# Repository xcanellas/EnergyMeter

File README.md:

## Descripción

Desarrollo completo, desde la tarjeta electrónica hasta el firmware, de un dispositivo que nos permite leer el consumo eléctrico y enviarlo mediante MQTT al servidor.

## Autor
**Xavier Cañellas**

* [Linkedin] (https://www.linkedin.com/in/xcanellas/)
* [Proyectos personales] (http://xnmundo.com/)

## Contacto
Si quieres contactarme puedes escribirme a xcanellas@xnmundo.com para consultas.

## Lincencia
MIT Public License v3.0
No puede usarse comercialmente.

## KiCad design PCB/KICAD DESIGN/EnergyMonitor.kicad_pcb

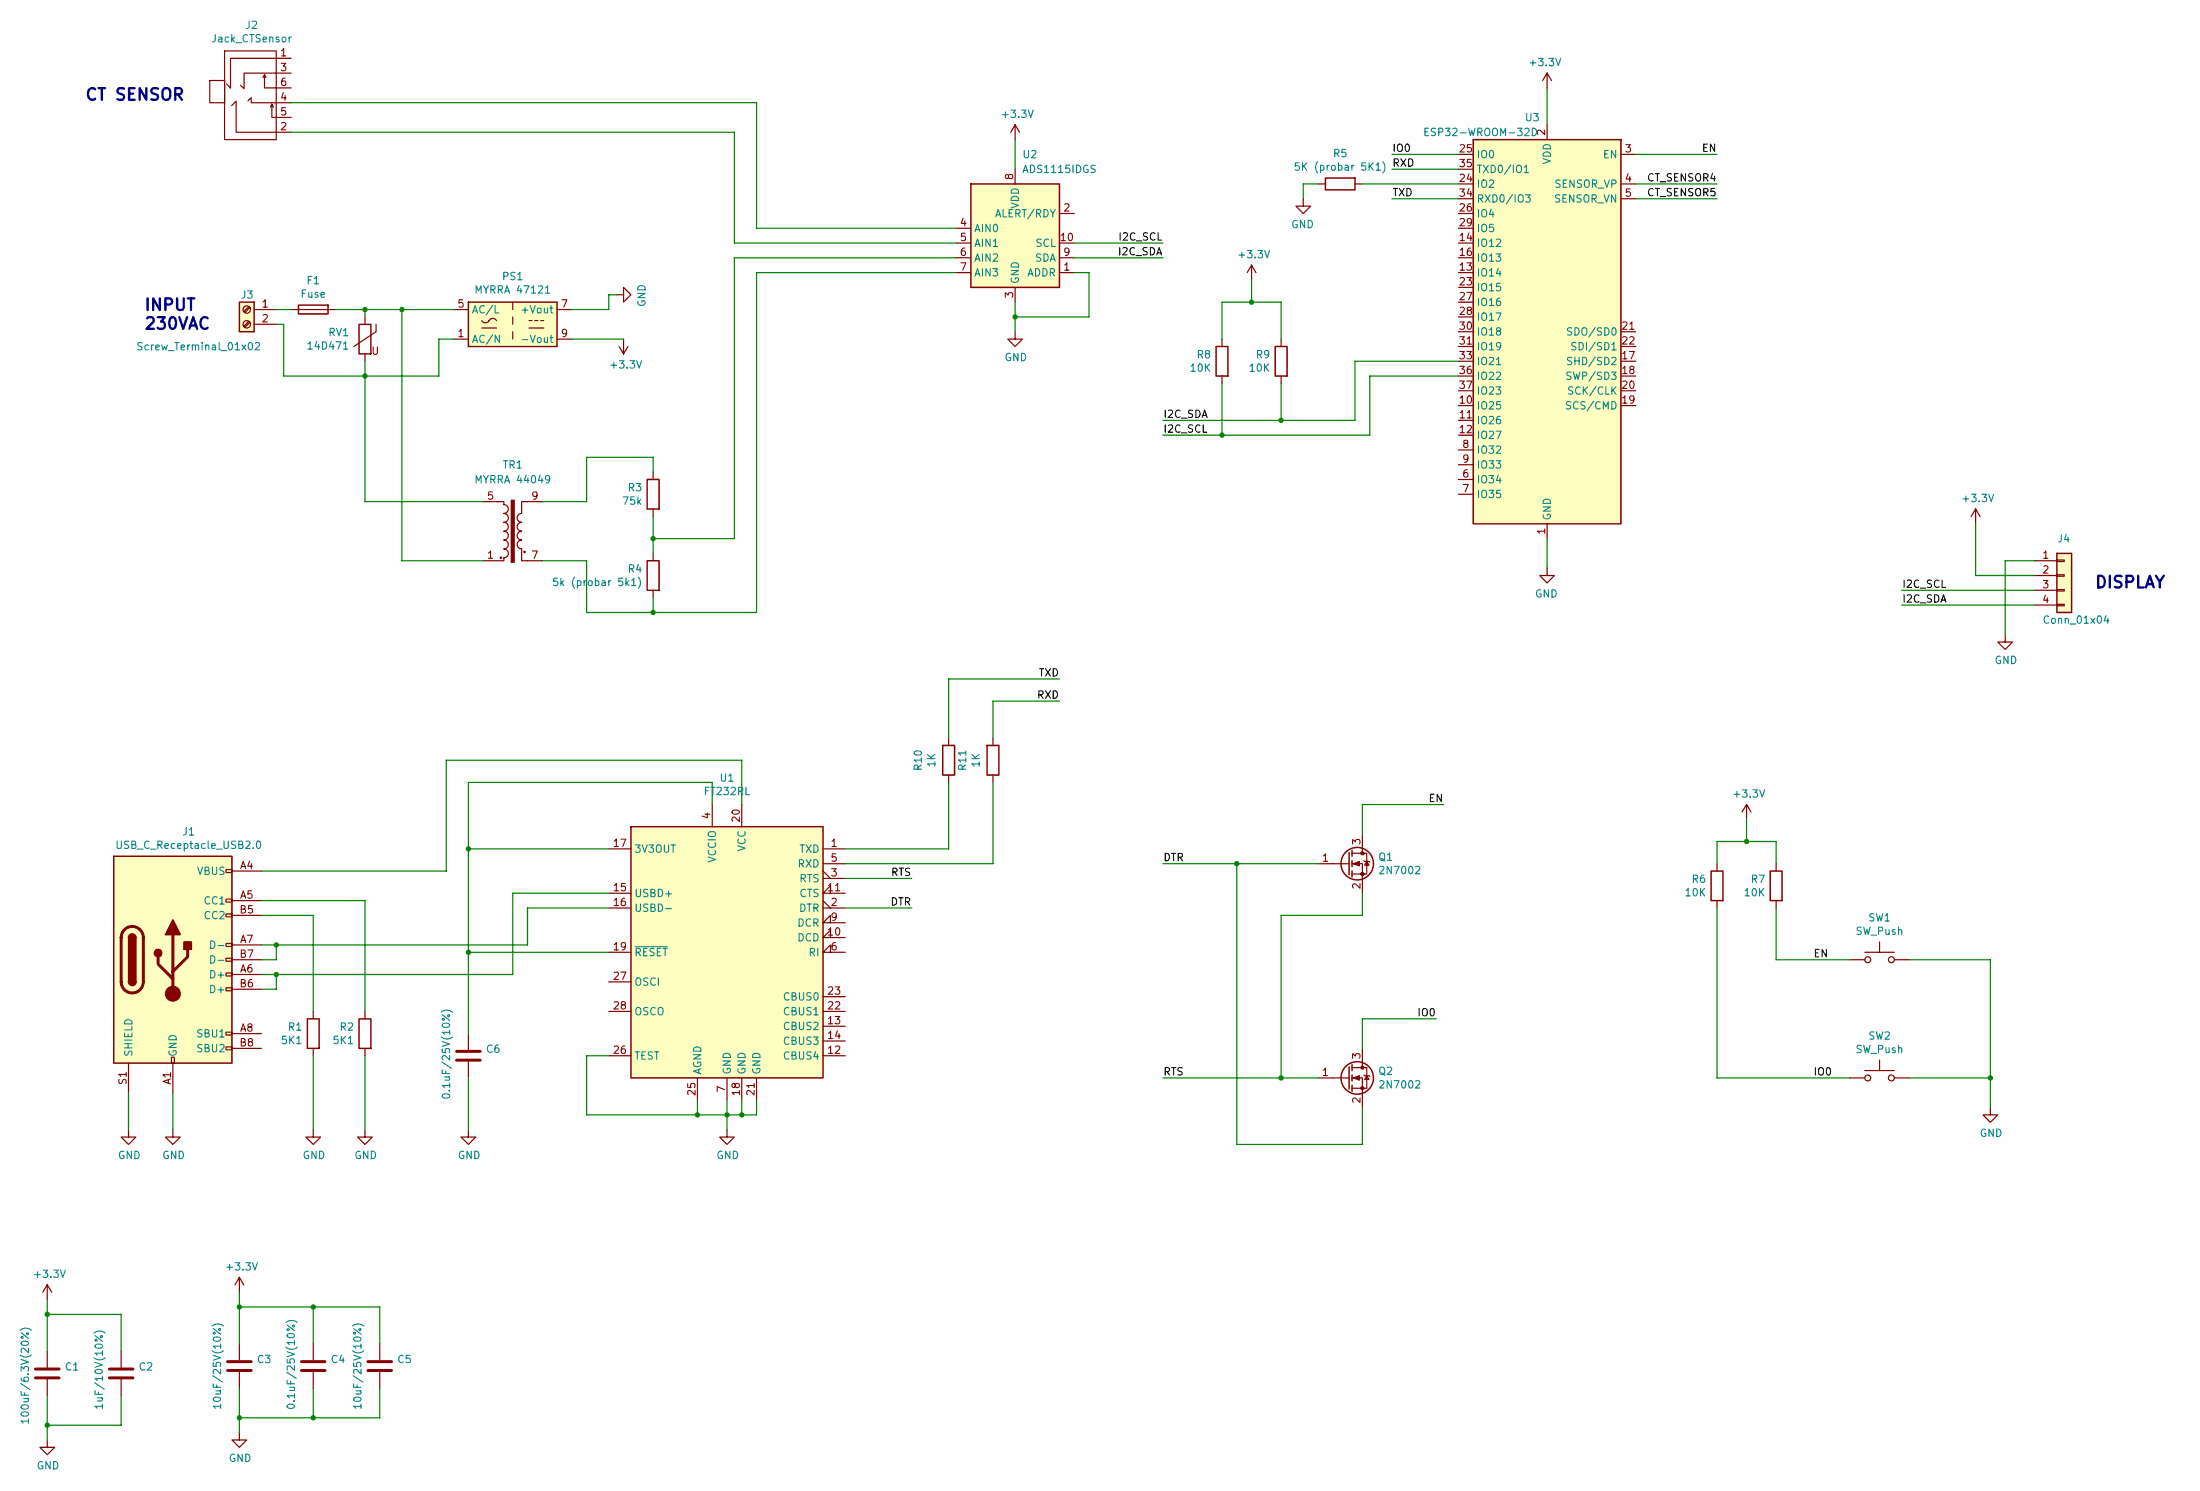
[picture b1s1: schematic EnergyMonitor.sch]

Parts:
C1: 100uF/6.3V(20%); C_0805_2012Metric
C2: 1uF/10V(10%); C_0805_2012Metric
C3, C5: 10uF/25V(10%); C_0805_2012Metric
C4, C6: 0.1uF/25V(10%); C_0805_2012Metric
F1: Fuse; Fuseholder_Cylinder-5x20mm_Schurter_0031_8201_Horizontal_Op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
J1: USB_C_Receptacle_USB2.0; USB_C_Receptacle_HRO_TYPE-C-31-M-12
J2: Jack_CTSensor; Jack_3.5mm_PJ311_Horizontal
J3: Screw_Terminal_01x02; PhoenixContact_GMSTBVA_2,5_2-G_1x02_P7.50mm_Vertical
J4: Conn_01x04; PinHeader_1x04_P2.54mm_Vertical_SMD_Pin1Left
PS1: MYRRA 47121; Converter_ACDC_Hahn_HS-400xx_THT
Q1, Q2: 2N7002; SOT-23
R1, R2: 5K1; R_0805_2012Metric
R3: 75k; R_0805_2012Metric
R4: 5k (probar 5k1); R_0805_2012Metric
R5: 5K (probar 5K1); R_0805_2012Metric
R6, R7, R8, R9: 10K; R_0805_2012Metric
R10, R11: 1K; R_0805_2012Metric
RV1: 14D471; RV_Disc_D12mm_W3.9mm_P7.5mm
SW1, SW2: SW_Push; SW_Push_1P1T_NO_CK_KMR2
TR1: MYRRA 44049; Converter_ACDC_Hahn_HS-400xx_THT
U1: FT232RL; SSOP-28_5.3x10.2mm_P0.65mm
U2: ADS1115IDGS; TSSOP-10_3x3mm_P0.5mm
U3: ESP32-WROOM-32D; ESP32-WROOM-32

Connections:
+3V3: C1.1, C2.1, C3.1, C4.1, C5.1, J4.2, PS1.9 (-Vout), R6.1, R7.1, R8.1, R9.1, U2.8 (VDD), U3.2 (VDD)
/CT_SENSOR4: U3.4 (SENSOR_VP)
/CT_SENSOR5: U3.5 (SENSOR_VN)
/DTR: Q1.1 (G), Q2.2 (S), U1.2 (DTR)
/EN: Q1.3 (D), R7.2, SW1.1, U3.3 (EN)
/I2C_SCL: J4.3, R8.2, U2.10 (SCL), U3.36 (IO22)
/I2C_SDA: J4.4, R9.2, U2.9 (SDA), U3.33 (IO21)
/IO0: Q2.3 (D), R6.2, SW2.1, U3.25 (IO0)
/RTS: Q1.2 (S), Q2.1 (G), U1.3 (RTS)
/RXD: R11.2, U3.35 (TXD0/IO1)
/TXD: R10.2, U3.34 (RXD0/IO3)
GND: C1.2, C2.2, C3.2, C4.2, C5.2, C6.2, J1.A1 (GND), J1.A12 (GND), J1.B1 (GND), J1.B12 (GND), J1.S1 (SHIELD), J4.1, PS1.7 (+Vout), R1.2, R2.2, R5.1, SW1.2, SW2.2, U1.7 (GND), U1.18 (GND), U1.21 (GND), U1.25 (AGND), U1.26 (TEST), U2.1 (ADDR), U2.3 (GND), U3.1 (GND), U3.15 (GND), U3.38 (GND), U3.39 (GND)
unnamed: C6.1, U1.4 (VCCIO), U1.17 (3V3OUT), U1.19 (~RESET~)
unnamed: F1.1, J3.1
unnamed: F1.2, PS1.5 (AC/L), RV1.1, TR1.1
unnamed: J1.A4 (VBUS), J1.A9 (VBUS), J1.B4 (VBUS), J1.B9 (VBUS), U1.20 (VCC)
unnamed: J1.A5 (CC1), R2.1
unnamed: J1.A6 (D+), J1.B6 (D+), U1.15 (USBD+)
unnamed: J1.A7 (D-), J1.B7 (D-), U1.16 (USBD-)
unnamed: J1.B5 (CC2), R1.1
unnamed: J2.2, U2.5 (AIN1)
unnamed: J2.4, U2.4 (AIN0)
unnamed: J3.2, PS1.1 (AC/N), RV1.2, TR1.5
unnamed: R3.1, TR1.9
unnamed: R3.2, R4.1, U2.6 (AIN2)
unnamed: R4.2, TR1.7, U2.7 (AIN3)
unnamed: R5.2, U3.24 (IO2)
unnamed: R10.1, U1.1 (TXD)
unnamed: R11.1, U1.5 (RXD)

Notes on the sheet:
DISPLAY
INPUT 230VAC
CT SENSOR

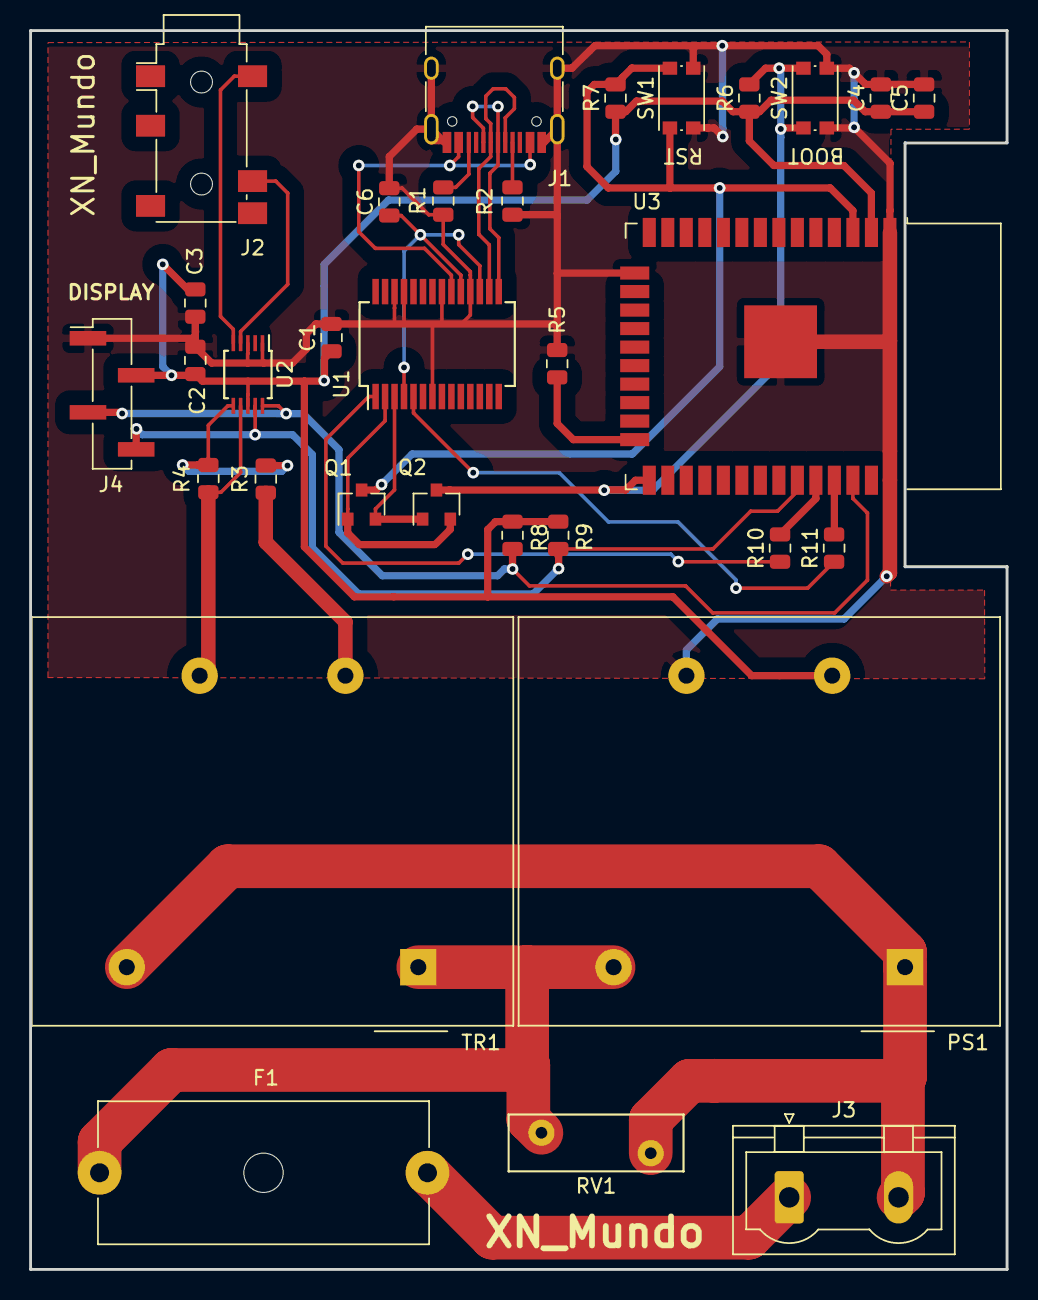
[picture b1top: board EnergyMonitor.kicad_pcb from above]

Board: 2 copper layers, 67.0 x 85.0 mm, 32 parts (0 on the bottom side), 27 nets.

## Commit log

2021-07-10 1st Release
2021-07-23 2nd release
2022-08-25 Creado README.md
